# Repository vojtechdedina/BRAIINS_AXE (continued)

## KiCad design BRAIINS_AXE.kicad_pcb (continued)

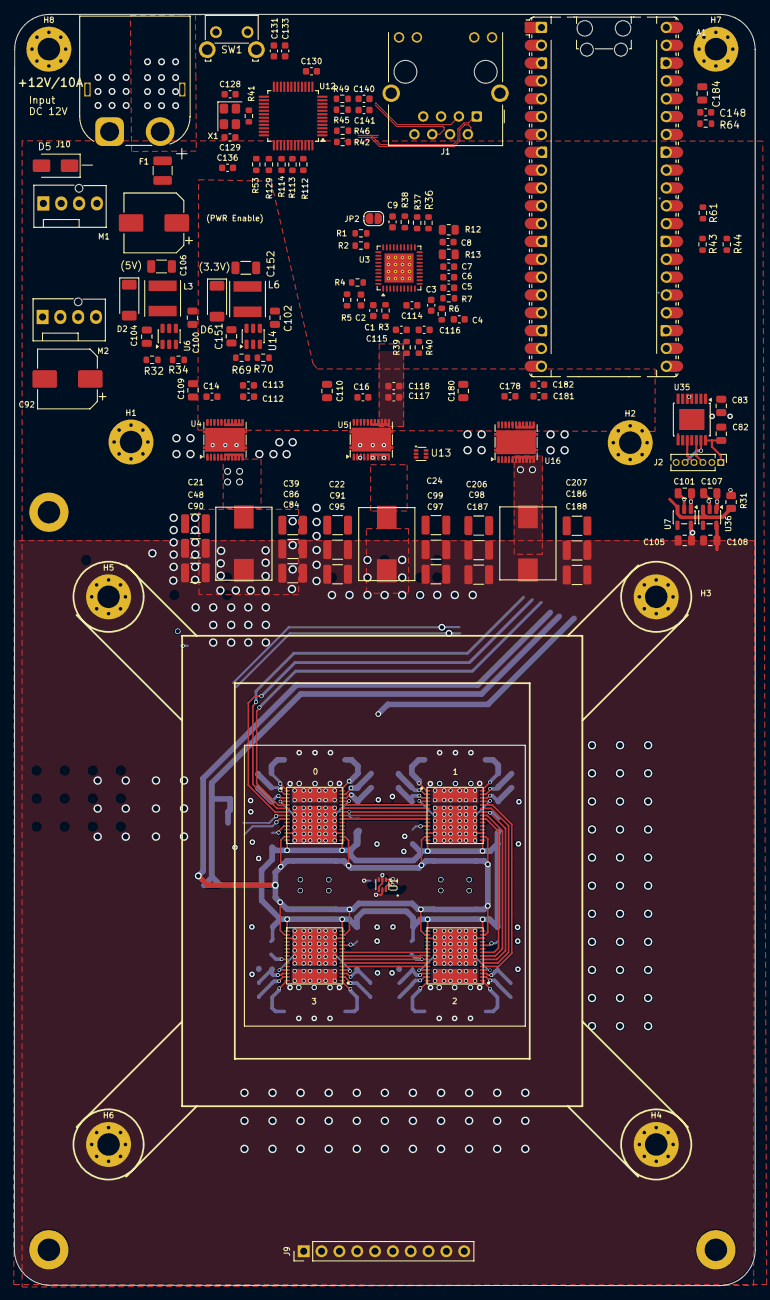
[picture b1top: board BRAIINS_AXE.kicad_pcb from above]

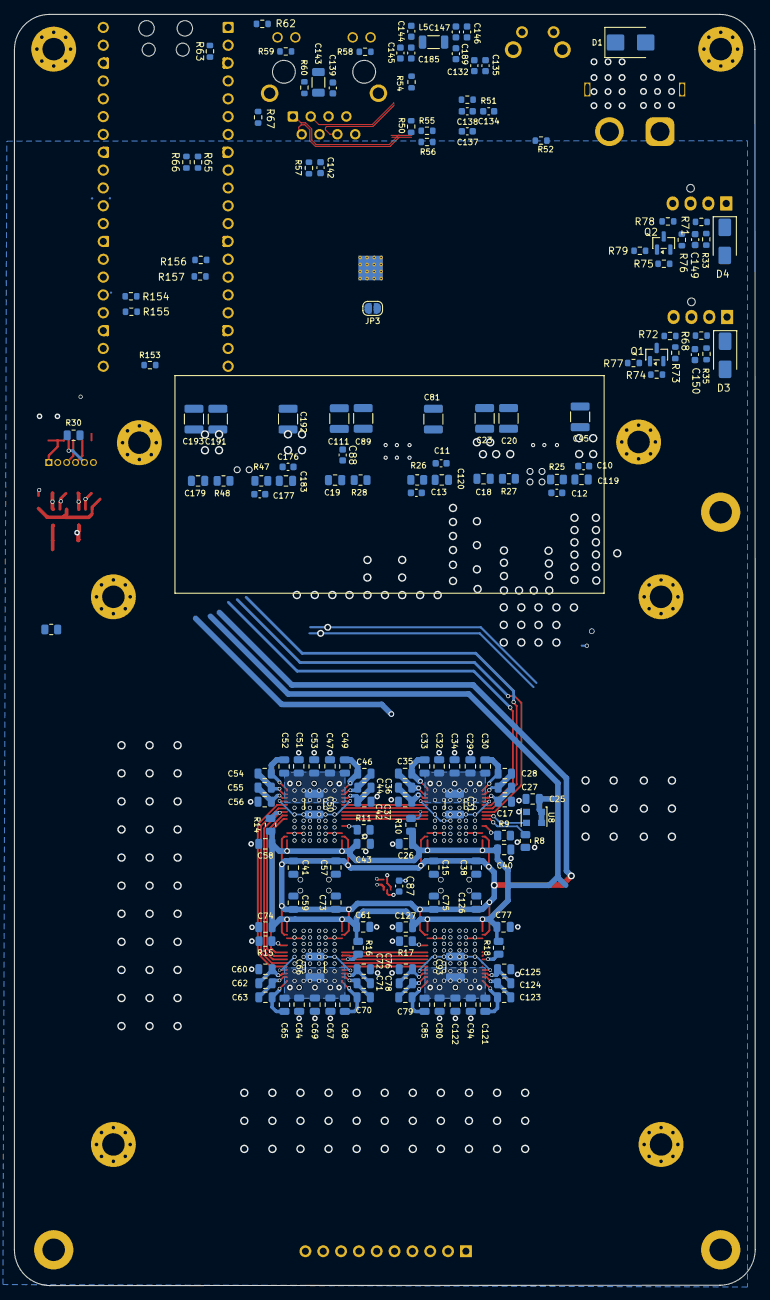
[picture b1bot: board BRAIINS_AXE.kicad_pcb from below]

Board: 6 copper layers, 105.5 x 181.1 mm, 303 parts (161 on the bottom side), 172 nets.

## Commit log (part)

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2026-06-25 POWER IN, OVLO, IDEAL DIODE
2026-06-25 power in components to PCB
2026-06-26 updated power stage placements
2026-06-26 power stage in place
2026-06-26 shrinking layout to fit
2026-06-26 optimizing pwr stage placement
2026-06-26 DC stage close to LGA socket
2026-06-26 alingment
2026-06-26 W5500
2026-06-26 3v3 eth
2026-06-27 minor updates
2026-06-27 rp2350 module in place
2026-06-27 placing W5500
2026-06-27 w5500 placed
2026-06-27 updated to LGA1700
2026-06-27 rp2350 connections
2026-06-27 fans
2026-06-27 sch_ should be ready
2026-06-27 controller resitors in place
2026-06-27 all components placed
2026-06-28 polygons
2026-06-28 ROUTING W5500
2026-06-28 W5500 ROUTED
2026-06-28 FANS ROUTED
2026-06-28 logic dc bucks routed
2026-06-28 VRM routing
2026-06-28 routing planes, asics
2026-06-28 routing last controls
2026-06-28 almost routed
2026-06-28 routed
2026-06-28 DRC OK
2026-06-28 minor tuning
2026-06-28 edits
2026-06-28 4mm NPTH mounting holes
2026-06-28 updated to JLCPCB 7628 stackup
2026-06-29 Add clearence for heatsing
2026-06-29 Change micro symbol to uF
2026-06-29 Add GND polygon to in4 layer
2026-06-29 Add schottky diode to rp pico vbus
2026-06-30 Add LCSC number to components
2026-06-30 Better 5V polygon connection
2026-06-30 Add missing LCSC number
2026-06-30 Use only stock component and unified LCSC capacitor code
